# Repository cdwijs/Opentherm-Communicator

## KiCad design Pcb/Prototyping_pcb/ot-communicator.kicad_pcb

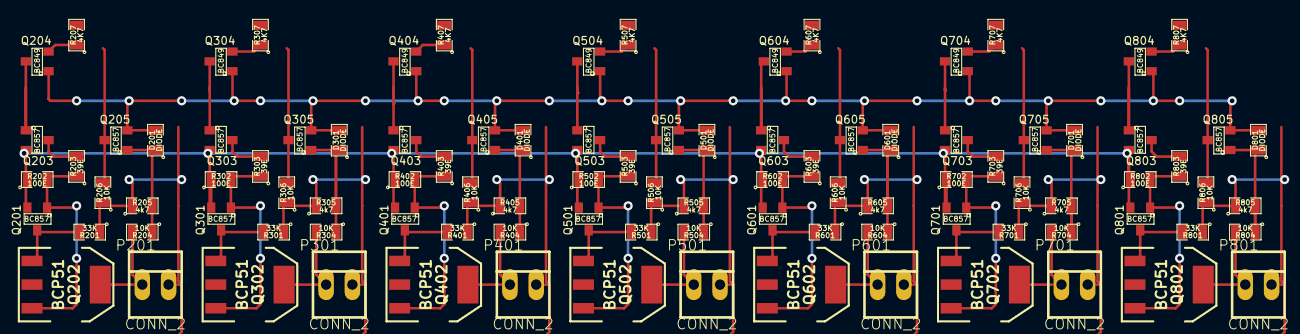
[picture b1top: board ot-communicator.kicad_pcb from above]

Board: 2 copper layers, 98 parts (0 on the bottom side), 59 nets.

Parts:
D201, D301, D401, D501, D601, D701, D801: DIODE; SM0805
P201, P301, P401, P501, P601, P701, P801: CONN_2; PINHEAD1-2
Q201, Q203, Q205, Q301, Q303, Q305, Q401, Q403, Q405, Q501, Q503, Q505, Q601, Q603, Q605, Q701, Q703, Q705, Q801, Q803, Q805: BC857; SOT23
Q202, Q302, Q402, Q502, Q602, Q702, Q802: BCP51; SOT223
Q204, Q304, Q404, Q504, Q604, Q704, Q804: BC849; SOT23
R201, R301, R401, R501, R601, R701, R801: 33K; SM0805
R202, R302, R402, R502, R602, R702, R802: 100E; SM0805
R203, R303, R403, R503, R603, R703, R803: 39E; SM0805
R204, R206, R304, R306, R404, R406, R504, R506, R604, R606, R704, R706, R804, R806: 10K; SM0805
R205, R305, R405, R505, R605, R705, R805: 4k7; SM0805
R207, R307, R407, R507, R607, R707, R807: 4K7; SM0805

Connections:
+5V: D201.2, D301.2, D401.2, D501.2, D601.2, D701.2, D801.2, Q204.1, Q205.2, Q304.1, Q305.2, Q404.1, Q405.2, Q504.1, Q505.2, Q604.1, Q605.2, Q704.1, Q705.2, Q804.1, Q805.2
+24V: Q201.2, Q203.2, Q301.2, Q303.2, Q401.2, Q403.2, Q501.2, Q503.2, Q601.2, Q603.2, Q701.2, Q703.2, Q801.2, Q803.2, R202.1, R302.1, R402.1, R502.1, R602.1, R702.1, R802.1
/frontend2/out: Q205.3, R206.2
/frontend3/out: Q305.3, R306.2
/frontend4/out: Q405.3, R406.2
/frontend5/out: Q505.3, R506.2
/frontend6/out: Q605.3, R606.2
/frontend7/out: Q705.3, R706.2
/frontend8/out: Q805.3, R806.2
GND: P201.2, P301.2, P401.2, P501.2, P601.2, P701.2, P801.2, R201.1, R205.1, R206.1, R301.1, R305.1, R306.1, R401.1, R405.1, R406.1, R501.1, R505.1, R506.1, R601.1, R605.1, R606.1, R701.1, R705.1, R706.1, R801.1, R805.1, R806.1
unnamed: P201.1, Q202.4, R204.2
unnamed: Q201.1, Q202.3, R202.2, R203.1
unnamed: Q204.2, R207.1
unnamed: Q203.1, Q204.3
unnamed: Q203.3, R203.2
unnamed: D201.1, Q205.1, R204.1, R205.2
unnamed: Q201.3, Q202.1, R201.2
unnamed: P301.1, Q302.4, R304.2
unnamed: Q301.1, Q302.3, R302.2, R303.1
unnamed: Q304.2, R307.1
unnamed: Q303.1, Q304.3
unnamed: Q303.3, R303.2
unnamed: D301.1, Q305.1, R304.1, R305.2
unnamed: Q301.3, Q302.1, R301.2
unnamed: Q401.1, Q402.3, R402.2, R403.1
unnamed: Q402.4, R404.2
unnamed: Q404.2, R407.1
unnamed: Q403.1, Q404.3
unnamed: D401.1, Q405.1, R404.1, R405.2
unnamed: Q403.3, R403.2
unnamed: Q401.3, Q402.1, R401.2
unnamed: P501.1, Q502.4, R504.2
unnamed: Q501.1, Q502.3, R502.2, R503.1
unnamed: Q504.2, R507.1
unnamed: Q503.1, Q504.3
unnamed: D501.1, Q505.1, R504.1, R505.2
unnamed: Q503.3, R503.2
unnamed: Q501.3, Q502.1, R501.2
unnamed: P601.1, Q602.4, R604.2
unnamed: Q601.1, Q602.3, R602.2, R603.1
unnamed: Q604.2, R607.1
unnamed: Q603.1, Q604.3
unnamed: D601.1, Q605.1, R604.1, R605.2
unnamed: Q603.3, R603.2
unnamed: Q601.3, Q602.1, R601.2
unnamed: Q703.1, Q704.3
unnamed: P401.1, P701.1, Q702.4, R704.2
unnamed: Q701.1, Q702.3, R702.2, R703.1
unnamed: Q704.2, R707.1
unnamed: D701.1, Q705.1, R704.1, R705.2
unnamed: Q703.3, R703.2
unnamed: Q701.3, Q702.1, R701.2
unnamed: P801.1, Q802.4, R804.2
unnamed: Q801.1, Q802.3, R802.2, R803.1
unnamed: Q804.2, R807.1
unnamed: Q803.1, Q804.3
unnamed: D801.1, Q805.1, R804.1, R805.2
unnamed: Q803.3, R803.2
unnamed: Q801.3, Q802.1, R801.2

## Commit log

2013-04-06 Initial commit. License and disclaimer done. No code yet, initial comments on decoding manchester
2013-04-06 Documented manchester Rx / Tx state machines Added GPL license file
2013-04-07 Added initial prototyping PCB, ot transmitter and receivers implemented
2013-04-07 removed some unneeded files
2013-04-08 Added state machine documentation for a conversation with a thermostat
2013-04-14 Added timeout handling while waiting for startbit in flowcharts Initial state machine code removed build files
2013-04-21 100usec interrupt timing done, tested by blinking LED on actual uC
2013-04-22 added initial initalisation of variables
2013-04-29 First successful loopback test in simulator, not tested with hardware
2013-05-02 moved common parts of the state machines into their own files, so adding a channel is more easy. Initial ot-comm code
2013-05-08 First actual conversation with a honeywell modulation thermostat: -Added routines to report opentherm conversation via serial port -input pins now actually work, ie, not analog pins -fixed manchester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
2013-05-08 serial output is now compatible with opentherm monitor 3.3 (http://www.tclcode.com/opentherm/download.html#utilities) added framework to send meaningfull data to the thermostat. For now only flame st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
2013-05-09 Splitted manchester transmitters and receivers in order to support multiple thermostats
2013-05-09 multiplied ot-comm code, but still only one thermostat reply's
2013-05-09 working converstation with 3 thermostats
2013-05-23 splitted manchester TX and RX routines
2013-05-23 First successfull conversation with 7 thermostats. Modified all routines to use banked RAM, now the variables for all thermostats are accessable Multiplied all routines for 8 thermostats Initial port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
2015-11-29 Now the setpoint of the thermostats can be altered from the PC side Added initial development guide
2015-11-29 Initial code to set flame and boiler indicators on the thermostat screen
2015-11-29 development guide now reflects the move from sourceforge to github
2015-11-29 Copyright is now 2013-2015
2015-11-29 Rewritten serial command handler. Flame and boiler bits now update correctly, but they are not yet correctly send to the thermostats. Keep alive message ignored for now
2015-11-29 Correction: fixed polarity of the flame command
2015-11-29 First try to show domestic hot water symbol (doesn't work yet)
